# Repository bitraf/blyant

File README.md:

# Bitraf's musikalske blyant
Et elektronikk byggesett for å lære seg å lodde, som du også kan ha masse morro med. Settet er laget til [Bitraf's Crowdfunding kampanje i 2021](https://www.spleis.no/project/175973). Om du vil ha et sett nå etter kampanjen, kan du besøke Bitraf i Brenneriveien 9 og kjøpe ditt eget sett i Bitmart.

Byggesettet er basert på Drawdio og alle filene redistribueres her under samme lisens (CC BY-SA 3.0). Bitraf's version was made by [jenschr](https://github.com/jenschr). Based on work by Jay Silver in the Lifelong Kindergarten group at the MIT Media Lab (CC BY-SA 3.0). 

## Instruksjoner
For å bygge settet trenger du en loddebolt, en avbiter-tang og litt loddetinn. Om du ikke har dette kan du stikke innom Bitraf og låne utstyr hos oss. Følg [instruksjonene du finner her](instruksjoner/instruksjoner.md), så kommer du i mål.

### Innhold i settet
* Blyant
* Kobber-tape
* Tegnestift
* 2 strips/buntebånd
* Lilla kretskort
* Høyttaler
* 300k brun motstand (R2)
* 10k liten, oransje motstand (R1)
* 0.1uF oransje kondensator (C2)
* 680pF blå kondensator (C3)
* 100uF polarisert kondensator (C1)
* PN2222 transistor
* PN2907ATF transistor
* TLC551CP chip
* Chip-holder
* 2 Batteri-holdere

## skjematikk
Skjematikk for kretskortet finnes i form av [PDF](BitrafDrawdio_skjematikk.pdf) og komplette [Kicad-filer](kretskort/).

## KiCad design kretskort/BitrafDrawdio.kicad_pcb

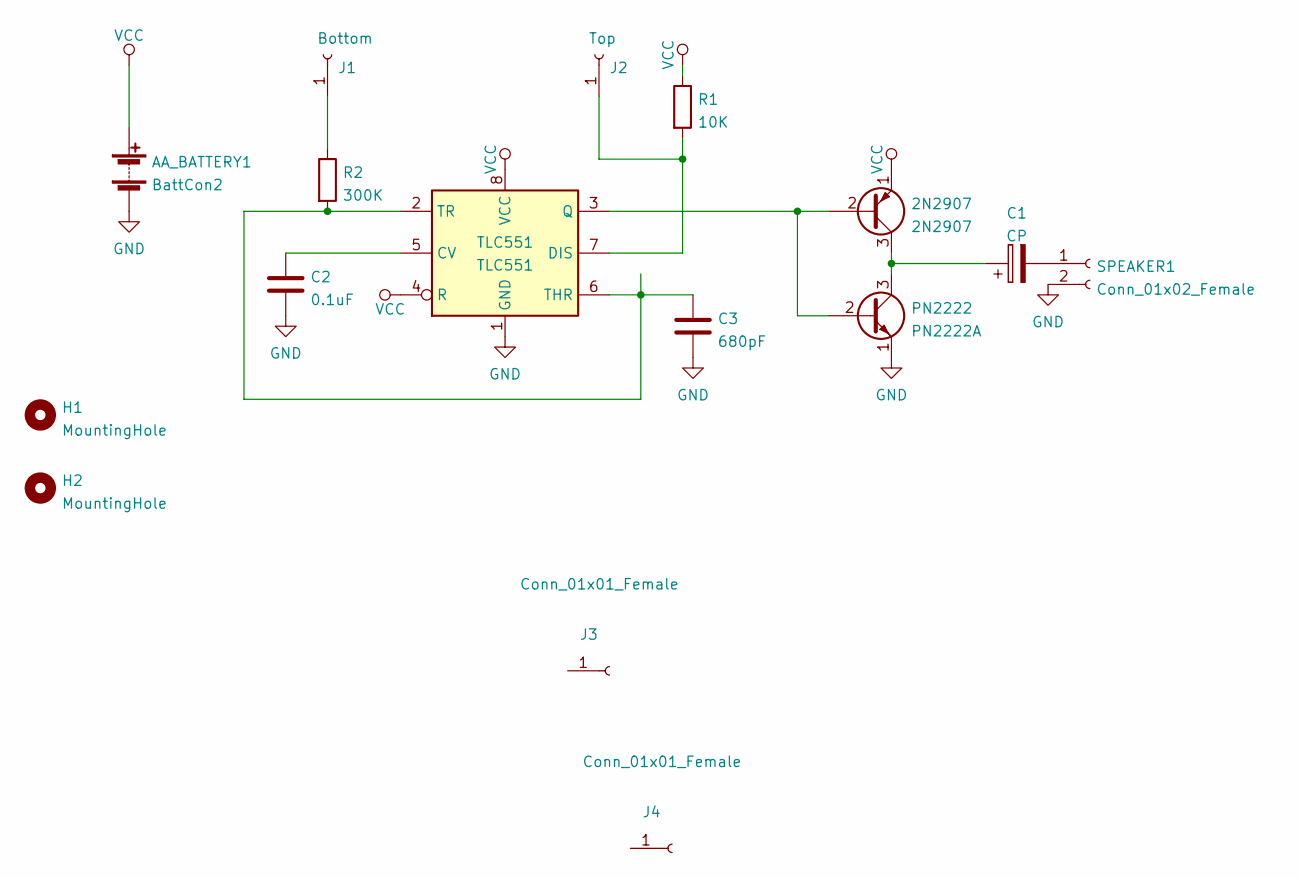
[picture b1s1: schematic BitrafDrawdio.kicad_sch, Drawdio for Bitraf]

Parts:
2N2907: 2N2907; TO-92_Inline_Wide; MPN PN2907ATF
AA_BATTERY1: BattCon2; DrawdioBatteryHolderAA; MPN BK92 (x2)
C1: CP; CP_Radial_D5.0mm_P2.00mm; MPN 6.3MS7100MEFCTZ5X7
C2: 0.1uF; C_Disc_D3.8mm_W2.6mm_P2.50mm; MPN K104K10X7RF5UH5
C3: 680pF; C_Disc_D3.8mm_W2.6mm_P2.50mm; MPN FA18C0G1H681JNU00
H1, H2: MountingHole; DrawdioStripsHole
J1: Bottom; DrawdioPad
J2: Top; DrawdioPad
J3: Conn_01x01_Female; Bitraf_Logo_31_x_12_mm
J4: Conn_01x01_Female; Bitraf_logo_3.0_x_7.5_mm
PN2222: PN2222A; TO-92_Inline_Wide; MPN PN2222ATF
R1: 10K; R_Axial_DIN0207_L6.3mm_D2.5mm_P5.08mm_Vertical; MPN CFR-12JB-52-10K
R2: 300K; R_Axial_DIN0207_L6.3mm_D2.5mm_P10.16mm_Horizontal; MPN RR01J300KTB
SPEAKER1: Conn_01x02_Female; DrawdioSpeaker; MPN CMS-160925-078S-67
TLC551: TLC551; DIP-8_W7.62mm_Socket_LongPads; MPN TLC551CP

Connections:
GND: AA_BATTERY1.2 (-), C2.2, C3.2, PN2222.1 (E), SPEAKER1.2, TLC551.1 (GND)
unnamed: 2N2907.2 (B), PN2222.2 (B), TLC551.3 (Q)
unnamed: 2N2907.3 (C), C1.1, PN2222.3 (C)
unnamed: C1.2, SPEAKER1.1
unnamed: C2.1, TLC551.5 (CV)
unnamed: C3.1, R2.2, TLC551.2 (TR), TLC551.6 (THR)
unnamed: J1.1, R2.1
unnamed: J2.1, R1.2, TLC551.7 (DIS)
VCC: 2N2907.1 (E), AA_BATTERY1.1 (+), R1.1, TLC551.4 (R), TLC551.8 (VCC)

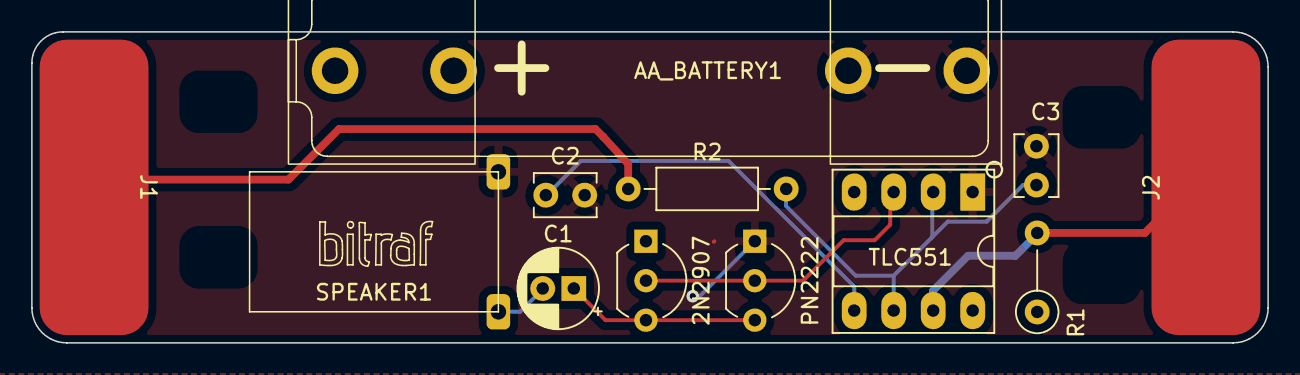
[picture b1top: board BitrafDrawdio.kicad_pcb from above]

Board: 2 copper layers, 79.5 x 20.0 mm, 16 parts (1 on the bottom side), 9 nets.

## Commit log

2022-01-15 first public commit
2022-01-15 corrections
2024-12-16 Typo

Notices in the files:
kretskort/BitrafDrawdio.kicad_sch:
Bitraf (CC BY-SA 3.0)
